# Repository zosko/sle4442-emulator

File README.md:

# SLE4442 Emulator
This is a smartcard emulator for ATMEGA8 microcontroller.

## Schematic

## Schematic

## Instructions
- Modify the "memory.h" file with the data of the card that you want to emulate
- If you compile the file with "#define BACKDOOR" uncommented, you will emulate a card that will be unlocked using any PSC code. Also, the PSC code sent by the reader will be updated immediately on the Security memory.  
- **WARNING**  
The maximum input clock frequency will be around 35KHz, not the 50KHz specified in the SLE4442 datasheet. I've tried my best to optimize the code but this is the main limitation of this project, you can try to use an external 16MHz clock for a better performance.

Real scheme used from https://github.com/sonovice/sle4442.

# Programming instruction
```
brew tap osx-cross/avr
brew install avr-gcc avrdude
```

The following commands are for USBasp programmer. For other programmers, look at the avrdude documentation.  

## Writing fuses
Execute those commands only one time, no need to write fuses every time you burn the flash.
```
make fuses
```

## Burning
Go in `code` folder. Execute this command:

```
make flash
```

## Read EEPROM
Once the PSC is grabbed, you can read the microcontroller EEPROM using this command:
```
make read
```

Open **eeprom.hex** with a text editor, PSC is present here:

## Sponsorship

**This project is proudly sponsored by [PCBWay](https://pcbway.com).**

PCBWay specializes in manufacturing high-quality printed circuit boards (PCBs), making them accessible and affordable for both hobbyists and professionals.

Their range of services includes:

- PCB prototyping
- Assembly services
- Instant order quotations
- Expert verification processes
- A user-friendly, hassle-free ordering system

I'm sincerely grateful to PCBWay for their generous support in making this project possible.

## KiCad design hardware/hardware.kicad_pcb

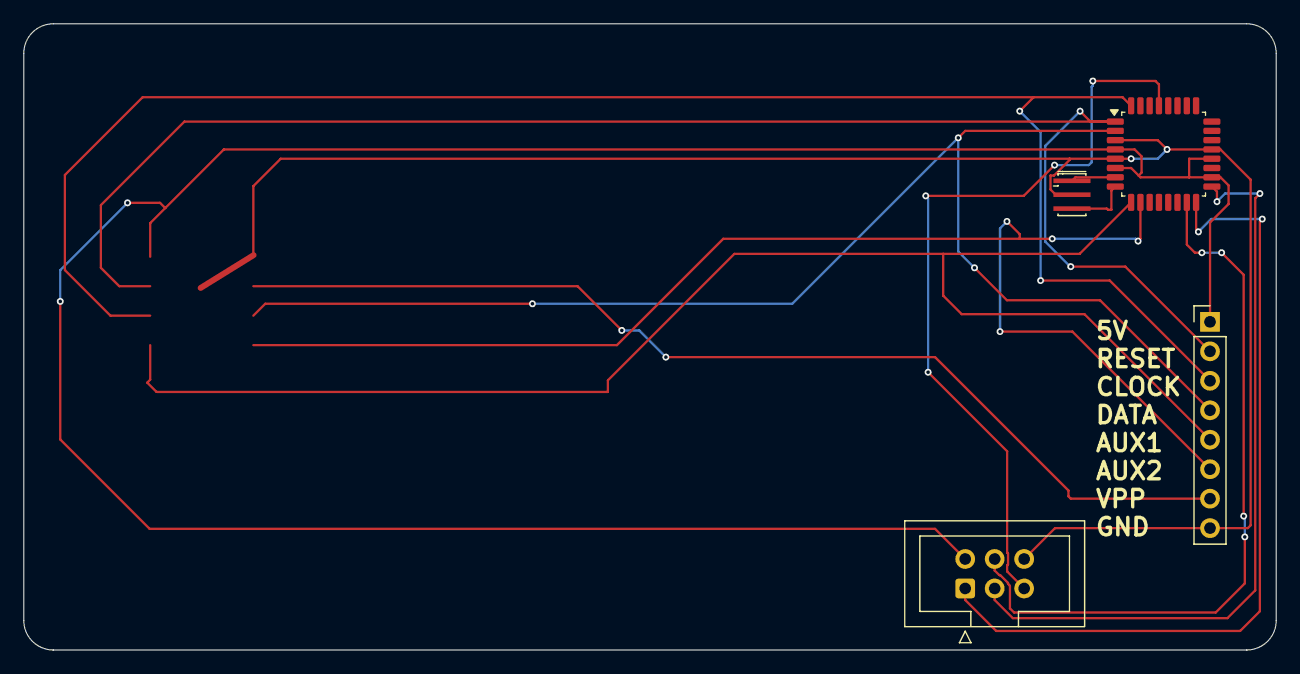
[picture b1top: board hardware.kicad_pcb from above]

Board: 2 copper layers, 108.0 x 54.0 mm, 4 parts (0 on the bottom side), 13 nets.

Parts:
J2: Pinouts; PinHeader_1x08_P2.54mm_Vertical
J4: AVR-ISP-6; IDC-Header_2x03_P2.54mm_Vertical
U1: ATmega8A-A; TQFP-32_7x7mm_P0.8mm
Y1: 16Mhz; Resonator_SMD_Murata_CSTxExxV-3Pin_3.0x1.1mm_HandSoldering

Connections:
+5V: J2.1, J4.2 (VCC), U1.4 (VCC), U1.6 (VCC), U1.18 (AVCC), U1.20 (AREF)
/AUX1: J2.5, U1.9 (PD5)
/AUX2: J2.6, U1.10 (PD6)
/CLOCK: J2.3, U1.32 (PD2)
/DATA: J2.4, U1.2 (PD4)
/ISP_RESET: J4.5 (~RST), U1.29 (PC6/~RESET)
/MISO: J4.1 (MISO), U1.16 (PB4)
/MOSI: J4.4 (MOSI), U1.15 (PB3)
/RESET: J2.2, U1.1 (PD3)
/SCK: J4.3 (SCK), U1.17 (PB5)
GND: J2.8, J4.6 (GND), U1.3 (GND), U1.5 (GND), U1.21 (AGND), Y1.2
unnamed: U1.7 (PB6/XTAL1), Y1.1
unnamed: U1.8 (PB7/XTAL2), Y1.3

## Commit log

2026-03-29 organized
2026-06-27 update bom
